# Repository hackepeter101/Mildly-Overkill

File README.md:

# Simple PLC-like Controller for Simple 24V Logic

## Specifications I am aiming for:

### Power & Protection
- 3S to 6S LiPo input support (including 24V)
- Onboard buck converter
- Reverse polarity protection
- Integrated fuse

### Motor Control
- 2x DC motor drivers (H-bridges)
- 3A current rating per bridge
- Current sensing at the H-bridges

### I/O & Interfaces
- Minimum of 8 total Inputs/Outputs (including H-bridge pins)
- STEMMA QT (I2C) connector
- USB-C port
- Physical Boot and Reset buttons

## Why
I have a project I need this for. I've built boards like this before and was never fully happy with how they turned out, so this is my chance to do it properly.

## Disclaimer: AI use
Every trace, every footprint and every questionable part choice on this board is mine. I placed and routed it all by hand. AI didn't draw a single line of copper. What I *am* doing is testing whether AI is any good at spotting my mistakes before a fab house turns them into expensive coasters.

`todo.md` was written entirely by AI. It's the list of everything it found. I read the suggestions, double-check them, and then fix them myself in KiCad, usually while muttering.

Still not sure a human made this? Read the commit history. It's an emotional journey. It goes from a confident "cirrcuit done" to "Insane amounts of routing" to "I cant do this anymore", then "Ill redo routing i guess", then "DONE!!!", and finally the very honest "Done for now". No AI writes commit messages that sound this tired.

*This section was also written with AI. The suffering in the commit history was not.*

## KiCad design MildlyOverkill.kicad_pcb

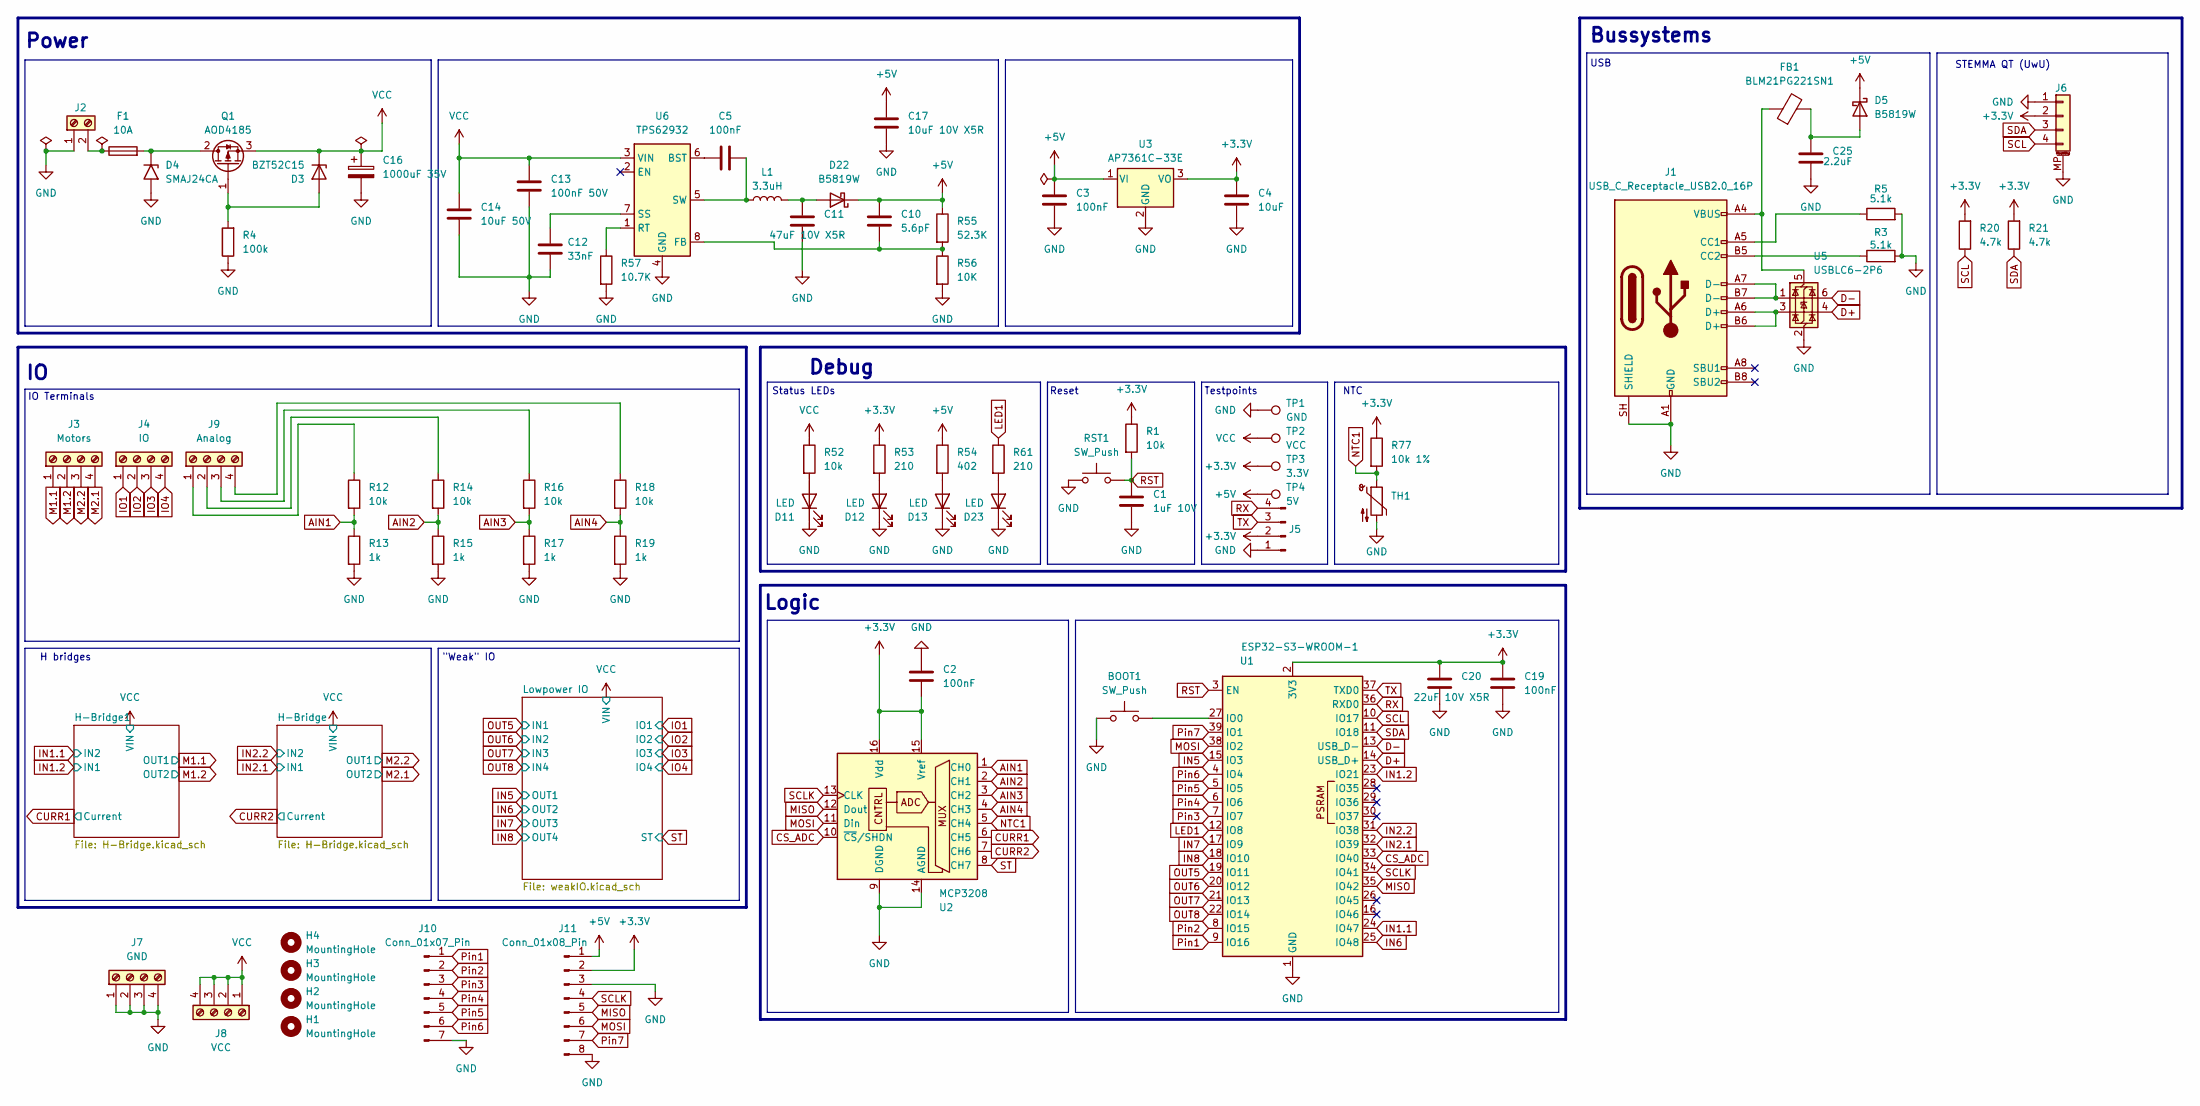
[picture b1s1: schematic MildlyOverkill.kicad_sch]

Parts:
BOOT1: SW_Push; SW_SPST_PTS647_Sx50
C1: 1uF 10V; C_0603_1608Metric
C2, C3, C5, C19: 100nF; C_0603_1608Metric
C4: 10uF; C_1206_3216Metric
C10: 5.6pF; C_0603_1608Metric
C11: 47uF 10V X5R; C_0805_2012Metric
C12: 33nF; C_0603_1608Metric
C13: 100nF 50V; C_0603_1608Metric
C14: 10uF 50V; C_1210_3225Metric
C16: 1000uF 35V; CP_Radial_D16.0mm_P7.50mm
C17: 10uF 10V X5R; C_0603_1608Metric
C20: 22uF 10V X5R; C_0603_1608Metric
C25: 2.2uF; C_1206_3216Metric
D3: BZT52C15; D_SOD-123
D4: SMAJ24CA; D_SMA
D5, D22: B5819W; D_SOD-123
D11, D12, D13, D23: LED; LED_0603_1608Metric
F1: 10A; Fuseholder_Blade_Mini_Keystone_3568
FB1: BLM21PG221SN1; L_0805_2012Metric
H1, H2, H3, H4: MountingHole; MountingHole_2.1mm
J1: USB_C_Receptacle_USB2.0_16P; USB_C_Receptacle_HRO_TYPE-C-31-M-12
J2: Screw_Terminal_01x02; PhoenixContact_MSTBA_2,5_2-G_1x02_P5.00mm_Horizontal
J3: Motors; TerminalBlock_Phoenix_MPT-0,5-4-2.54_1x04_P2.54mm_Horizontal
J4: IO; TerminalBlock_Phoenix_MPT-0,5-4-2.54_1x04_P2.54mm_Horizontal
J5: Conn_01x04_Pin; PinHeader_1x04_P2.54mm_Vertical
J6: Conn_01x04_MountingPin; JST_SH_BM04B-SRSS-TB_1x04-1MP_P1.00mm_Vertical
J7: GND; TerminalBlock_Phoenix_MPT-0,5-4-2.54_1x04_P2.54mm_Horizontal
J8: VCC; TerminalBlock_Phoenix_MPT-0,5-4-2.54_1x04_P2.54mm_Horizontal
J9: Analog; TerminalBlock_Phoenix_MPT-0,5-4-2.54_1x04_P2.54mm_Horizontal
J10: Conn_01x07_Pin; PinSocket_1x07_P2.54mm_Vertical
J11: Conn_01x08_Pin; PinSocket_1x08_P2.54mm_Vertical
L1: 3.3uH; WE-XHMI 4.3x4.3
Q1: AOD4185; TO-252-2
R1, R12, R14, R16, R18, R52: 10k; R_0603_1608Metric
R3, R5: 5.1k; R_0603_1608Metric
R4: 100k; R_0603_1608Metric
R13, R15, R17, R19: 1k; R_0603_1608Metric
R20, R21: 4.7k; R_0805_2012Metric_Pad1.20x1.40mm_HandSolder
R53, R61: 210; R_0603_1608Metric
R54: 402; R_0603_1608Metric
R55: 52.3K; R_0603_1608Metric
R56: 10K; R_0603_1608Metric
R57: 10.7K; R_0603_1608Metric
R77: 10k 1%; R_0603_1608Metric
RST1: SW_Push; SW_SPST_PTS647_Sx50
TH1: NCP18XH103F03RB; R_0805_2012Metric_Pad1.20x1.40mm_HandSolder
TP1: GND; TestPoint_Loop_D2.50mm_Drill1.85mm
TP2: VCC; TestPoint_Loop_D2.50mm_Drill1.85mm
TP3: 3.3V; TestPoint_Loop_D2.50mm_Drill1.85mm
TP4: 5V; TestPoint_Loop_D2.50mm_Drill1.85mm
U1: ESP32-S3-WROOM-1
U2: MCP3208; SOIC-16_3.9x9.9mm_P1.27mm
U3: AP7361C-33E; SOT-223-3_TabPin2
U5: USBLC6-2P6; SOT-666
U6: TPS62932; SOT-583-8

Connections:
+3.3V: C2.2, C4.1, C19.1, C20.1, J5.2, J6.2, J11.2, R1.1, R20.2, R21.2, R53.1, R77.1, TP3.1 (1_1), U1.2 (3V3), U2.15 (Vref), U2.16 (Vdd), U3.3 (VO); also elsewhere on the board
+5V: C3.1, C10.2, C17.2, D5.1 (K), D22.1 (K), J11.1, R54.1, R55.1, TP4.1 (1_1), U3.1 (VI)
AIN1: R12.2, R13.1, U2.1 (CH0)
AIN2: R14.2, R15.1, U2.2 (CH1)
AIN3: R16.2, R17.1, U2.3 (CH2)
AIN4: R18.2, R19.1, U2.4 (CH3)
CS_ADC: U1.33 (IO40), U2.10 (~CS/SHDN)
CURR1: U2.6 (CH5); also elsewhere on the board
CURR2: U2.7 (CH6); also elsewhere on the board
D+: U1.14 (USB_D+), U5.4 (I/O2)
D-: U1.13 (USB_D-), U5.6 (I/O1)
GND: BOOT1.1, C1.2, C2.1, C3.2, C4.2, C11.1, C12.1, C13.1, C14.1, C16.2, C17.1, C19.2, C20.2, C25.2, D4.2 (A2), D11.1 (K), D12.1 (K), D13.1 (K), D23.1 (K), J1.A1 (GND), J1.A12 (GND), J1.B1 (GND), J1.B12 (GND), J1.SH (SHIELD), J2.1, J5.1, J6.1, J6.MP (MountPin), J7.1, J7.2, J7.3, J7.4, J10.7, J11.3, J11.8, R3.2, R4.1, R5.2, R13.2, R15.2, R17.2, R19.2, R56.2, R57.2, RST1.1, TH1.2, TP1.1 (1_1), U1.1 (GND), U1.40 (GND), U1.41 (GND), U2.9 (DGND), U2.14 (AGND), U3.2 (GND), U5.2 (GND), U6.4 (GND); also elsewhere on the board
IN1.1: U1.24 (IO47); also elsewhere on the board
IN1.2: U1.23 (IO21); also elsewhere on the board
IN2.1: U1.32 (IO39); also elsewhere on the board
IN2.2: U1.31 (IO38); also elsewhere on the board
IN5: U1.15 (IO3); also elsewhere on the board
IN6: U1.25 (IO48); also elsewhere on the board
IN7: U1.17 (IO9); also elsewhere on the board
IN8: U1.18 (IO10); also elsewhere on the board
IO1: J4.1; also elsewhere on the board
IO2: J4.2; also elsewhere on the board
IO3: J4.3; also elsewhere on the board
IO4: J4.4; also elsewhere on the board
LED1: R61.1, U1.12 (IO8)
M1.1: J3.1; also elsewhere on the board
M1.2: J3.2; also elsewhere on the board
M2.1: J3.4; also elsewhere on the board
M2.2: J3.3; also elsewhere on the board
MISO: J11.5, U1.35 (IO42), U2.12 (Dout)
MOSI: J11.6, U1.38 (IO2), U2.11 (Din)
NTC1: R77.2, TH1.1, U2.5 (CH4)
unnamed: D3.2 (A), Q1.1 (G), R4.2
unnamed: D4.1 (A1), F1.2, Q1.2 (D)
unnamed: C25.1, D5.2 (A), FB1.2
unnamed: D11.2 (A), R52.2
unnamed: D12.2 (A), R53.2
unnamed: D13.2 (A), R54.2
unnamed: C11.2, D22.2 (A), L1.2
unnamed: D23.2 (A), R61.2
unnamed: J1.A5 (CC1), R5.1
unnamed: J1.B5 (CC2), R3.1
unnamed: J1.A6 (D+), J1.B6 (D+), U5.3 (I/O2)
unnamed: J1.A7 (D-), J1.B7 (D-), U5.1 (I/O1)
unnamed: F1.1, J2.2
unnamed: J9.1, R12.1
unnamed: J9.2, R14.1
unnamed: J9.3, R16.1
unnamed: J9.4, R18.1
unnamed: BOOT1.2, U1.27 (IO0)
unnamed: FB1.1, J1.A4 (VBUS), J1.A9 (VBUS), J1.B4 (VBUS), J1.B9 (VBUS), U5.5 (VBUS)
unnamed: C5.1, U6.6 (BST)
unnamed: C10.1, R55.2, R56.1, U6.8 (FB)
unnamed: R57.1, U6.1 (RT)
unnamed: C12.2, U6.7 (SS)
unnamed: C5.2, L1.1, U6.5 (SW)
OUT5: U1.19 (IO11); also elsewhere on the board
OUT6: U1.20 (IO12); also elsewhere on the board
OUT7: U1.21 (IO13); also elsewhere on the board
OUT8: U1.22 (IO14); also elsewhere on the board
Pin1: J10.1, U1.9 (IO16)
Pin2: J10.2, U1.8 (IO15)
Pin3: J10.3, U1.7 (IO7)
Pin4: J10.4, U1.6 (IO6)
Pin5: J10.5, U1.5 (IO5)
Pin6: J10.6, U1.4 (IO4)
Pin7: J11.7, U1.39 (IO1)
RST: C1.1, R1.2, RST1.2, U1.3 (EN)
RX: J5.4, U1.36 (RXD0)
SCL: J6.4, R20.1, U1.10 (IO17)
SCLK: J11.4, U1.34 (IO41), U2.13 (CLK)
SDA: J6.3, R21.1, U1.11 (IO18)
ST: U2.8 (CH7); also elsewhere on the board
TX: J5.3, U1.37 (TXD0)
VCC: C13.2, C14.2, C16.1, D3.1 (K), J8.1, J8.2, J8.3, J8.4, Q1.3 (S), R52.1, TP2.1 (1_1), U6.3 (VIN); also elsewhere on the board

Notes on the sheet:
H bridges
Debug
IO Terminals
Power
Reset
NTC
Logic
Testpoints
STEMMA QT (UwU)
Bussystems
"Weak" IO
USB
Status LEDs

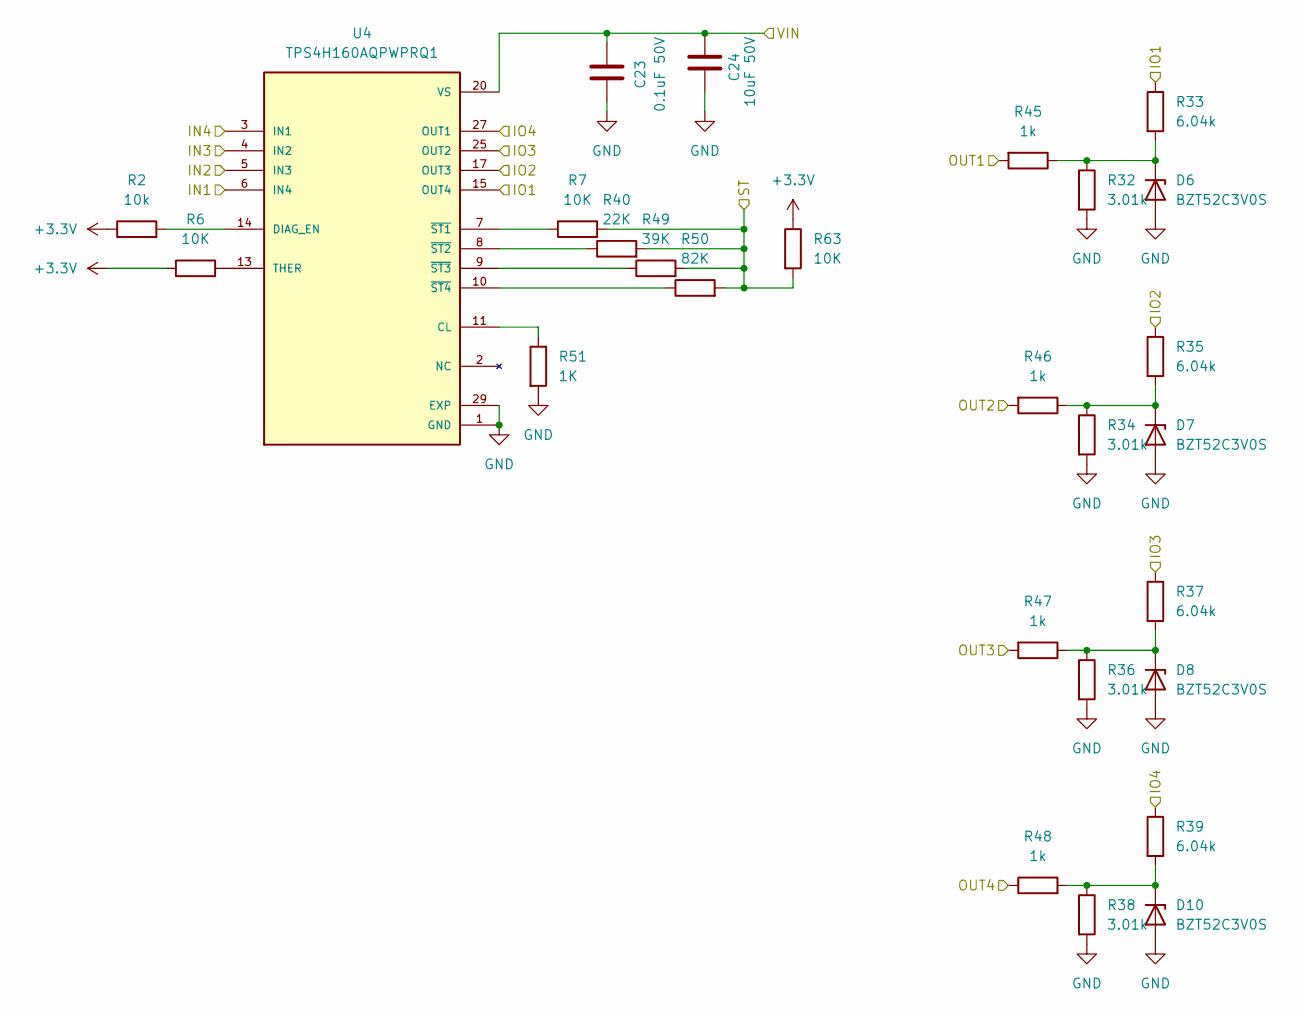
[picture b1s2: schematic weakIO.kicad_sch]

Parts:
C23: 0.1uF 50V; C_0603_1608Metric
C24: 10uF 50V; C_1210_3225Metric
D6, D7, D8, D10: BZT52C3V0S; D_SOD-323
R2: 10k; R_0603_1608Metric
R6, R7, R63: 10K; R_0603_1608Metric
R32, R34, R36, R38: 3.01k; R_0603_1608Metric
R33, R35, R37, R39: 6.04k; R_0603_1608Metric
R40: 22K; R_0603_1608Metric
R45, R46, R47, R48: 1k; R_0603_1608Metric
R49: 39K; R_0603_1608Metric
R50: 82K; R_0603_1608Metric
R51: 1K; R_0603_1608Metric
U4: TPS4H160AQPWPRQ1; IC_TPS4H160AQPWPRQ1; PARTREV D

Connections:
+3.3V: R2.1, R6.1, R63.1; also elsewhere on the board
GND: C23.1, C24.2, D6.2 (A), D7.2 (A), D8.2 (A), D10.2 (A), R32.2, R34.2, R36.2, R38.2, R51.2, U4.1 (GND), U4.12 (GND), U4.29 (EXP), U4.30 (EXP), U4.31 (EXP), U4.32 (EXP), U4.33 (EXP), U4.34 (EXP), U4.35 (EXP), U4.36 (EXP), U4.37 (EXP), U4.38 (EXP), U4.39 (EXP), U4.40 (EXP), U4.41 (EXP), U4.42 (EXP), U4.43 (EXP), U4.44 (EXP), U4.45 (EXP), U4.46 (EXP), U4.47 (EXP), U4.48 (EXP), U4.49 (EXP), U4.50 (EXP), U4.51 (EXP), U4.52 (EXP), U4.53 (EXP); also elsewhere on the board
IN5: R45.2; also elsewhere on the board
IN6: R46.2; also elsewhere on the board
IN7: R47.2; also elsewhere on the board
IN8: R48.1; also elsewhere on the board
IO1: R33.1, U4.15 (OUT4), U4.16 (OUT4); also elsewhere on the board
IO2: R35.1, U4.17 (OUT3), U4.18 (OUT3); also elsewhere on the board
IO3: R37.1, U4.25 (OUT2), U4.26 (OUT2); also elsewhere on the board
IO4: R39.1, U4.27 (OUT1), U4.28 (OUT1); also elsewhere on the board
unnamed: D6.1 (K), R32.1, R33.2, R45.1
unnamed: D7.1 (K), R34.1, R35.2, R46.1
unnamed: D8.1 (K), R36.1, R37.2, R47.1
unnamed: D10.1 (K), R38.1, R39.2, R48.2
unnamed: R51.1, U4.11 (CL)
unnamed: R2.2, U4.14 (DIAG_EN)
unnamed: R6.2, U4.13 (THER)
unnamed: R7.1, U4.7 (~ST1)
unnamed: R40.1, U4.8 (~ST2)
unnamed: R49.1, U4.9 (~ST3)
unnamed: R50.1, U4.10 (~ST4)
OUT5: U4.6 (IN4); also elsewhere on the board
OUT6: U4.5 (IN3); also elsewhere on the board
OUT7: U4.4 (IN2); also elsewhere on the board
OUT8: U4.3 (IN1); also elsewhere on the board
ST: R7.2, R40.2, R49.2, R50.2, R63.2; also elsewhere on the board
VCC: C23.2, C24.1, U4.20 (VS), U4.21 (VS), U4.22 (VS), U4.23 (VS); also elsewhere on the board

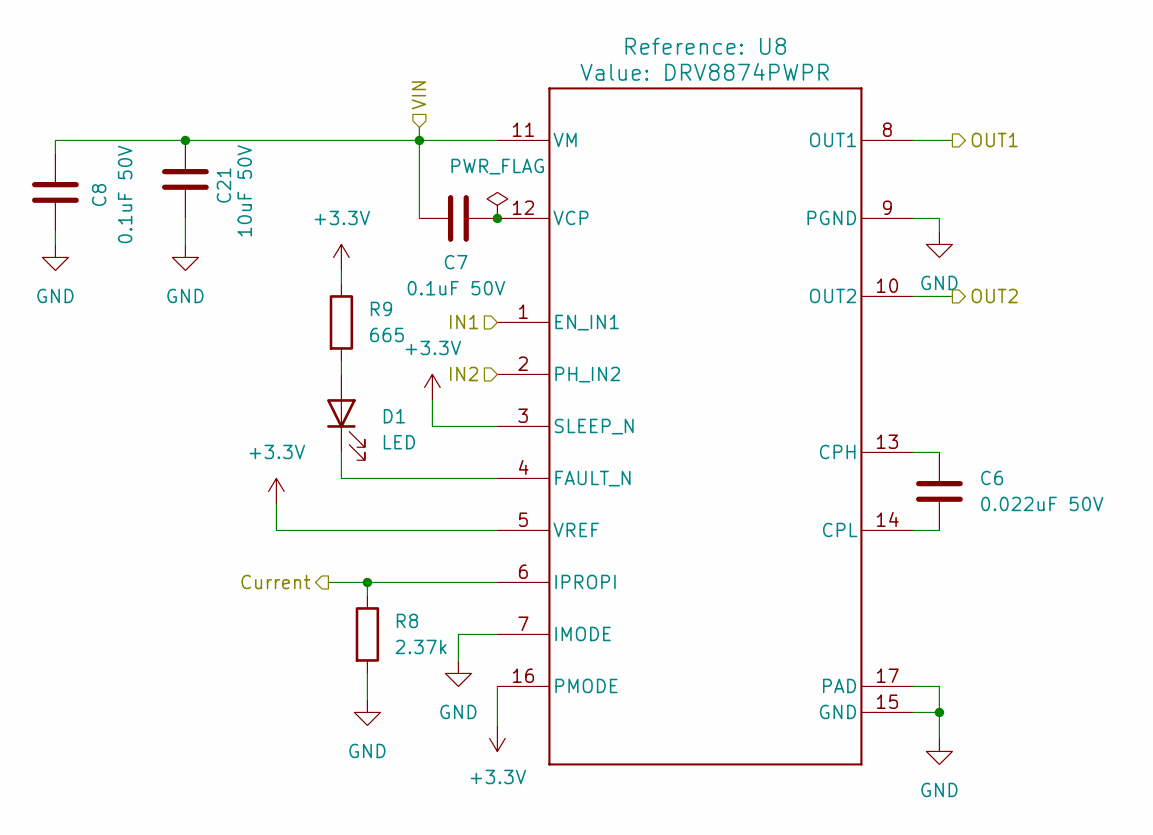
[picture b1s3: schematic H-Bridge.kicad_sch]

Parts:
C6: 0.022uF 50V; C_0603_1608Metric
C7, C8: 0.1uF 50V; C_0603_1608Metric
C21: 10uF 50V; C_1210_3225Metric
D1: LED; LED_0603_1608Metric
R8: 2.37k; R_0603_1608Metric
R9: 665; R_0603_1608Metric
U8: DRV8874PWPR; PWP0016J_L

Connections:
+3.3V: R9.1, U8.3 (SLEEP_N), U8.5 (VREF), U8.16 (PMODE); also elsewhere on the board
CURR2: R8.1, U8.6 (IPROPI); also elsewhere on the board
GND: C8.1, C21.2, R8.2, U8.7 (IMODE), U8.9 (PGND), U8.15 (GND), U8.17 (PAD); also elsewhere on the board
IN2.1: U8.1 (EN_IN1); also elsewhere on the board
IN2.2: U8.2 (PH_IN2); also elsewhere on the board
M2.1: U8.10 (OUT2); also elsewhere on the board
M2.2: U8.8 (OUT1); also elsewhere on the board
unnamed: D1.2 (A), R9.2
unnamed: D1.1 (K), U8.4 (FAULT_N)
unnamed: C6.1, U8.13 (CPH)
unnamed: C6.2, U8.14 (CPL)
unnamed: C7.2, U8.12 (VCP)
VCC: C7.1, C8.2, C21.1, U8.11 (VM); also elsewhere on the board

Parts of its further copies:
C9, C15: 0.1uF 50V; C_0603_1608Metric
C18: 0.022uF 50V; C_0603_1608Metric
C22: 10uF 50V; C_1210_3225Metric
D2: LED; LED_0603_1608Metric
R10: 665; R_0603_1608Metric
R11: 2.37k; R_0603_1608Metric
U9: DRV8874PWPR; PWP0016J_L

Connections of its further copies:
+3.3V: R10.1, U9.3 (SLEEP_N), U9.5 (VREF), U9.16 (PMODE); also elsewhere on the board
CURR1: R11.1, U9.6 (IPROPI); also elsewhere on the board
GND: C9.1, C22.2, R11.2, U9.7 (IMODE), U9.9 (PGND), U9.15 (GND), U9.17 (PAD); also elsewhere on the board
IN1.1: U9.2 (PH_IN2); also elsewhere on the board
IN1.2: U9.1 (EN_IN1); also elsewhere on the board
M1.1: U9.8 (OUT1); also elsewhere on the board
M1.2: U9.10 (OUT2); also elsewhere on the board
unnamed: D2.2 (A), R10.2
unnamed: D2.1 (K), U9.4 (FAULT_N)
unnamed: C18.1, U9.13 (CPH)
unnamed: C18.2, U9.14 (CPL)
unnamed: C15.2, U9.12 (VCP)
VCC: C9.2, C15.1, C22.1, U9.11 (VM); also elsewhere on the board

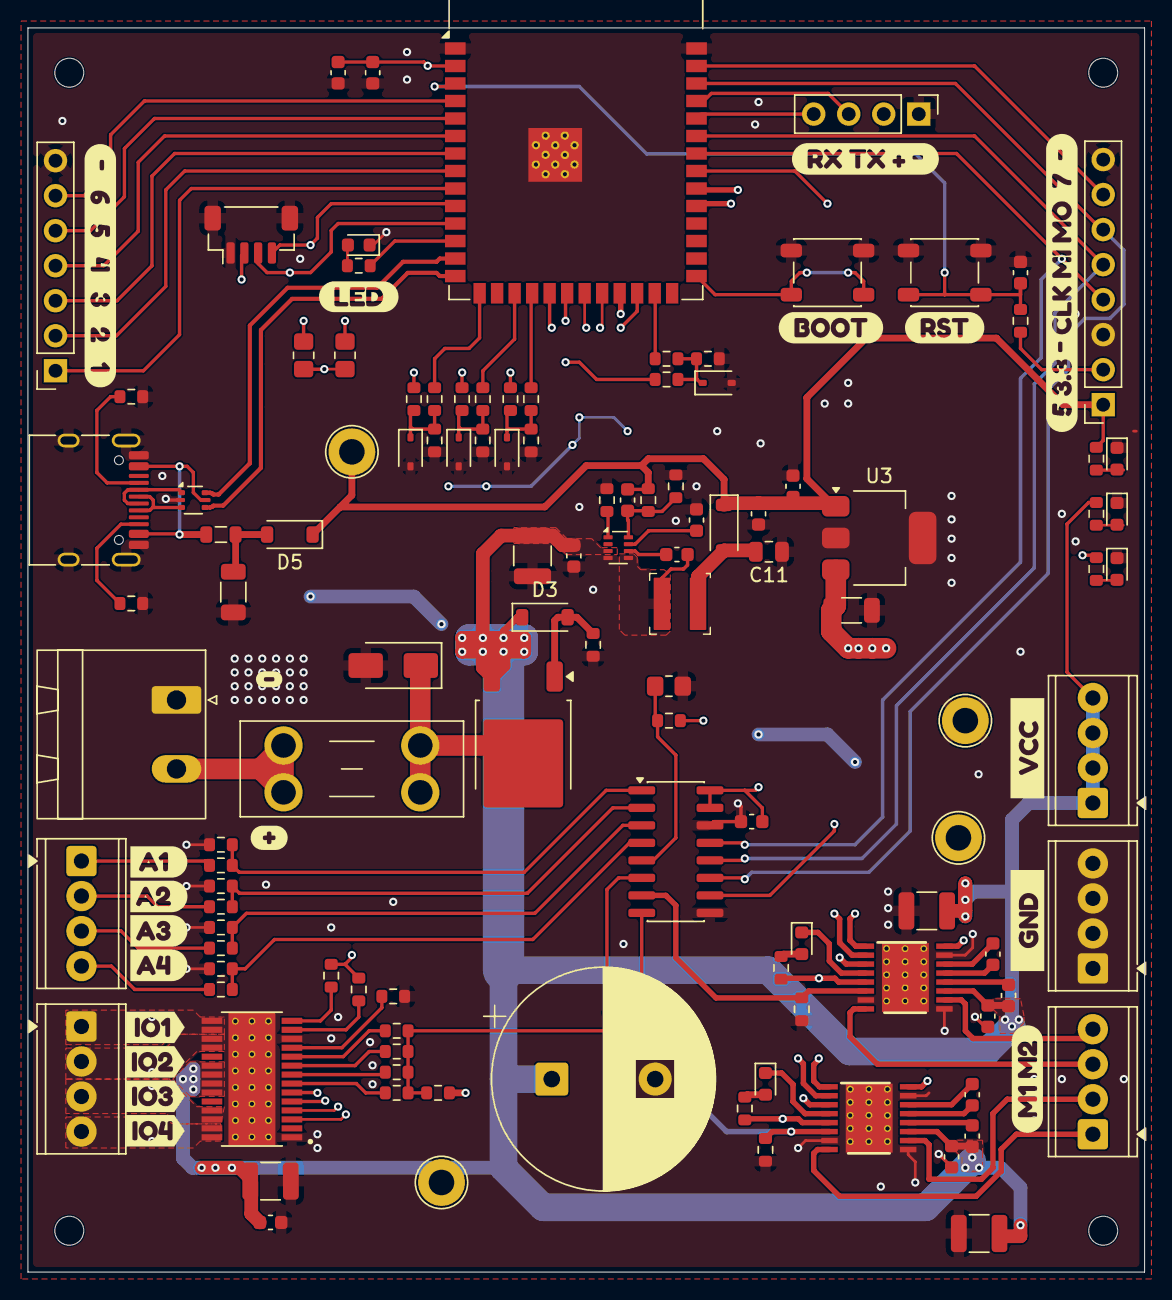
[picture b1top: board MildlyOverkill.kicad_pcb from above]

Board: 4 copper layers, 81.0 x 90.2 mm, 138 parts (0 on the bottom side), 96 nets.

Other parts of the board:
kibuzzard-6ACBD1B3: G***; kibuzzard-6ACBD1B3
kibuzzard-6ACBD3AA: G***; kibuzzard-6ACBD3AA
kibuzzard-6ACBD3B0: G***; kibuzzard-6ACBD3B0
kibuzzard-6ACBD3CF: G***; kibuzzard-6ACBD3CF
kibuzzard-6ACBD3D5: G***; kibuzzard-6ACBD3D5
kibuzzard-6ACBD5D3: G***; kibuzzard-6ACBD5D3
kibuzzard-6ACBD5E0: G***; kibuzzard-6ACBD5E0
kibuzzard-6ACBD34D: G***; kibuzzard-6ACBD34D
kibuzzard-6ACBD41A: G***; kibuzzard-6ACBD41A
kibuzzard-6ACBD50A: G***; kibuzzard-6ACBD50A
kibuzzard-6ACBD168: G***; kibuzzard-6ACBD168
kibuzzard-6ACBD341: G***; kibuzzard-6ACBD341
kibuzzard-6ACBD409: G***; kibuzzard-6ACBD409
kibuzzard-6ACBD410: G***; kibuzzard-6ACBD410
kibuzzard-6ACBD423: G***; kibuzzard-6ACBD423
kibuzzard-6ACBD433: G***; kibuzzard-6ACBD433
kibuzzard-6ACBD473: G***; kibuzzard-6ACBD473
kibuzzard-6ACBD573: G***; kibuzzard-6ACBD573
kibuzzard-6ACBE024: G***; kibuzzard-6ACBE024
